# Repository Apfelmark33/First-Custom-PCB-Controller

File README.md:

# Pathfinder 

A custom, password-protected PCB controller board that acts as a digital combination lock system. It's essentially a safe but without anything in it (yet). 

I used KICad to make the pbc and the arduino IDE for the code.

---

##  Project Overview

How it Works
Pathfinder is a simple electronic lock system that uses 3 buttons to enter a password. As you press the buttons, LEDs light up to show your progress, and a small speaker (piezo buzzer) plays different sounds to let you know if your password was right or wrong.

Key Features
Smart Code Checking: Instead of just adding numbers together (where the order doesn't matter), the board remembers the exact sequence of your button presses. If your password is "abc", typing "cba" won't open it!

Every time you press a button, an LED turns on. By the third press, all three LEDs light up so you know you've entered the full 3-character code (a 3 character code is necessary but it can always be changed in the firmware)

Sound Alerts: The system talks to you through sound (so you know it works). It plays a happy, double-beep if you get the password right, and a low, buzzing tone if you get it wrong (room for improvement).

## Schematic

## PCB Layout

## 3D Model

## Bill of Materials (BOM)

| Name | Purpose | Quantity | Total Cost (USD) | Link | Distributor |
| :--- | :--- | :---: | :---: | :--- | :--- |
| **Custom PCB** | PCB | 1 | 1.75 | [Link](https://cart.jlcpcb.com/quote?stencilLayer=1&stencilWidth=100&stencilLength=100&stencilCounts=5&plateType=1&spm=Jlcpcb.Homepage.1010) | JLCPCB |
| **Buzzer** | Sound | 5 | 1.15 | [Link](https://de.aliexpress.com/item/1005006260328559.html) | Aliexpress |
| **Resistor** | Resistor | 100 | 0.56 | [Link](https://de.aliexpress.com/item/1005006040209297.html) | Aliexpress |
| **LED** | Light (Output) | 100 | 0.74 | [Link](https://de.aliexpress.com/item/4000857337669.html) | Aliexpress |
| **Keyboard switch** | Input | 20 | 1.29 | [Link](https://de.aliexpress.com/item/1005011838889689.html) | Aliexpress |
| **XIAO RP2040** | PCB | 1 | 4.52 | [Link](https://de.aliexpress.com/item/1005006987582110.html) | Aliexpress |

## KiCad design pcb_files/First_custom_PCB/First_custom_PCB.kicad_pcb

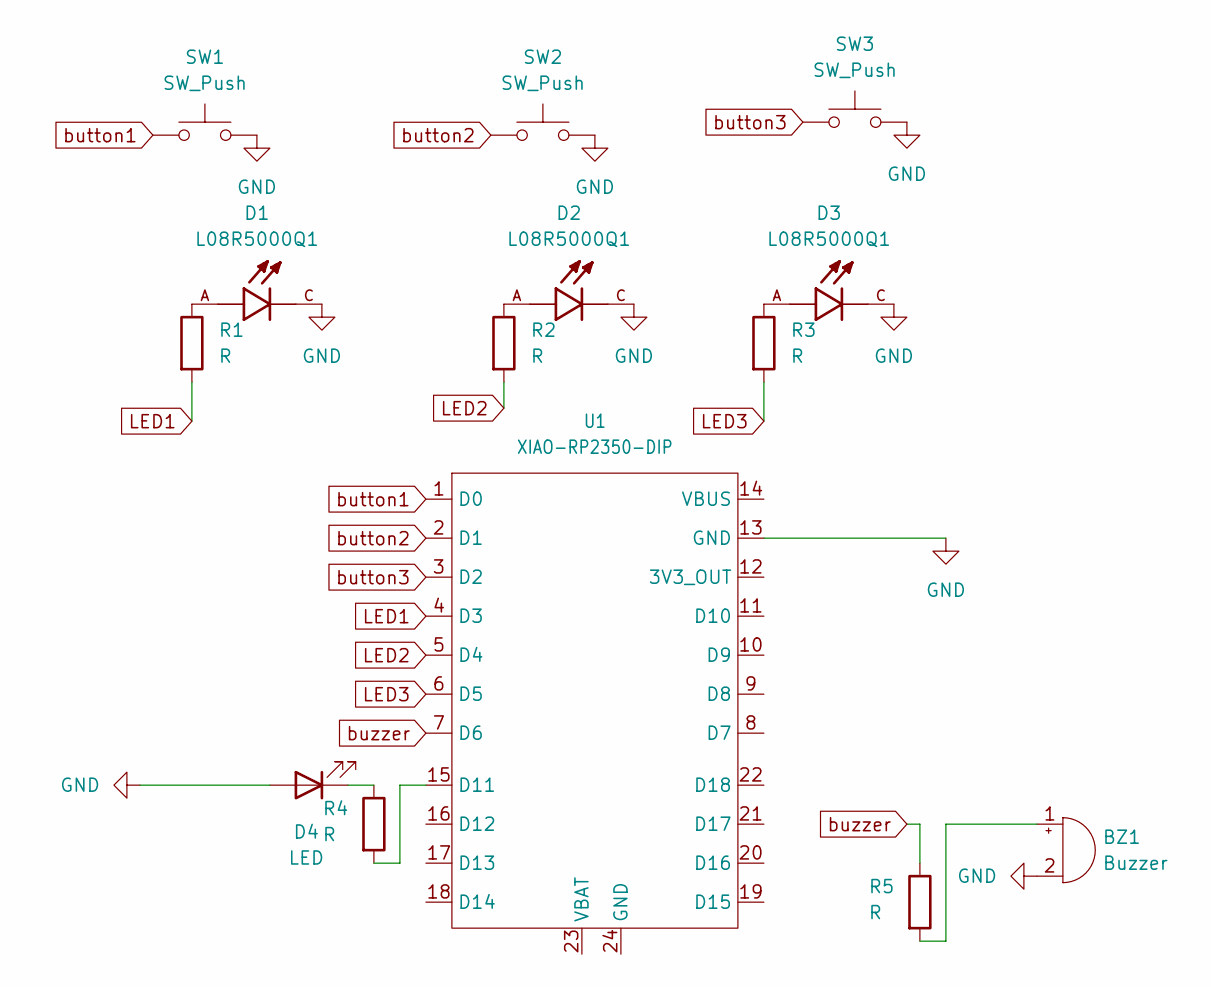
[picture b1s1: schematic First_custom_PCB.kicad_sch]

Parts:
BZ1: Buzzer; Buzzer_12x9.5RM7.6
D1, D2, D3: L08R5000Q1; LEDRD254W57D500H1070; PARTREV NA
D4: LED; LED_D5.0mm
R1, R2, R3, R4, R5: R; R_Axial_DIN0204_L3.6mm_D1.6mm_P5.08mm_Horizontal
SW1, SW2, SW3: SW_Push; SW_Cherry_MX_1.00u_PCB
U1: XIAO-RP2350-DIP

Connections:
GND: BZ1.2 (-), D1.C, D2.C, D3.C, D4.2 (A), SW1.2, SW2.2, SW3.2, U1.13 (GND)
LED1: R1.2, U1.4 (D3)
LED2: R2.2, U1.5 (D4)
LED3: R3.2, U1.6 (D5)
unnamed: BZ1.1 (+), R5.2
unnamed: D1.A, R1.1
unnamed: D2.A, R2.1
unnamed: D3.A, R3.1
unnamed: D4.1 (K), R4.1
unnamed: R4.2, U1.15 (D11)
button1: SW1.1, U1.1 (D0)
button2: SW2.1, U1.2 (D1)
button3: SW3.1, U1.3 (D2)
buzzer: R5.1, U1.7 (D6)

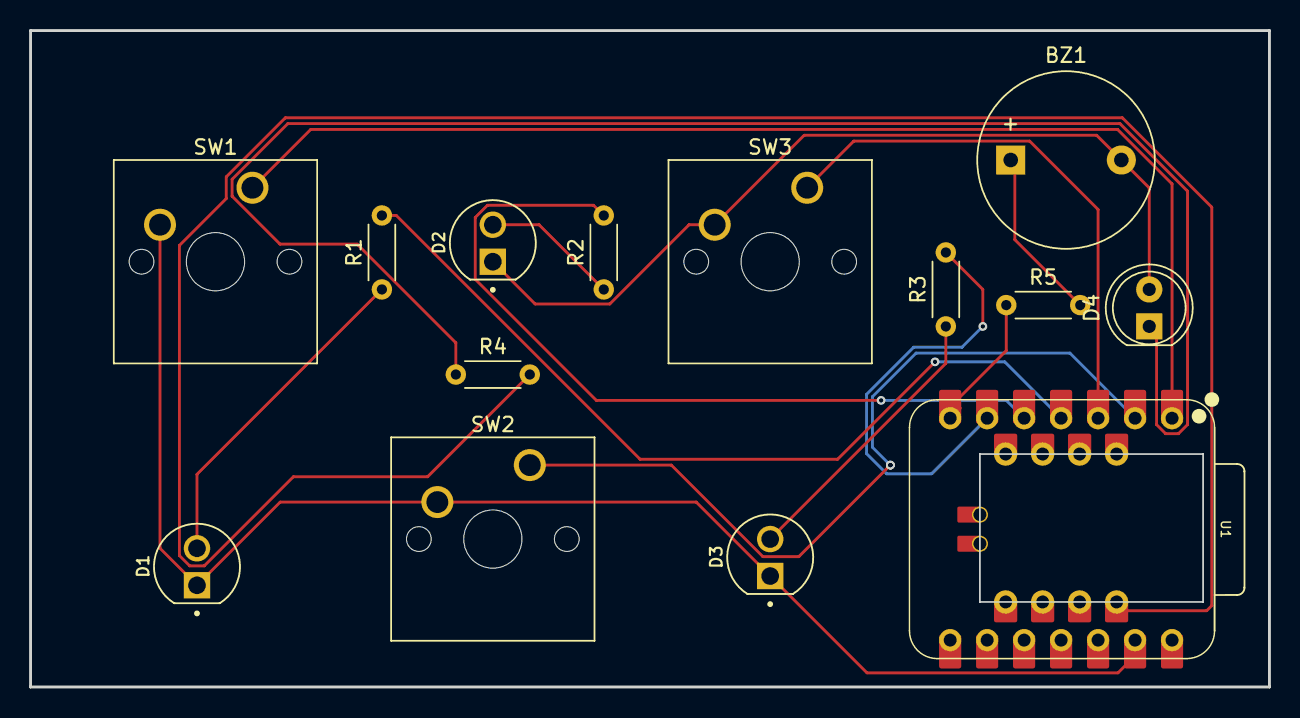
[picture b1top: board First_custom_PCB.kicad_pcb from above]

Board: 2 copper layers, 85.1 x 45.1 mm, 14 parts (0 on the bottom side), 14 nets.

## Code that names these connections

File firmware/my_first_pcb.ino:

int BUT1 = D0;
int BUT2 = D1;
int BUT3 = D2;

int LED1 = D3;
int LED2 = D4;
int LED3 = D5;

int SPEAKER = D6;
int light = D11; 


void setup() {
  // put your setup code here, to run once:

    
    pinMode(BUT1, INPUT_PULLUP);
    pinMode(BUT2, INPUT_PULLUP);
    pinMode(BUT3, INPUT_PULLUP);

    pinMode(LED1, OUTPUT);
     pinMode(LED2, OUTPUT);
    pinMode(LED3, OUTPUT);

 pinMode(SPEAKER, OUTPUT);

  pinMode(light, OUTPUT);
  digitalWrite(light, HIGH); //Standart light but customizable if necessary
}

void loop() {
  // put your main code here, to run repeatedly:

String input = "";
const String password = "abc";
boolean status = false;
for(int i= 0; i<3; i++){
while (status == false){


if(digitalRead(BUT1) == LOW){

tone(SPEAKER, 1000);
input = input +"a";
status = true;
delay(100);
}
else if(digitalRead(BUT2) == LOW){
  
tone(SPEAKER, 1000);
input = input +"b";
status = true;
delay(100);
}


else if(digitalRead(BUT3) == LOW){

tone(SPEAKER, 1000);
input = input +"c";
status = true;
delay(100);

}
}
noTone(SPEAKER);
status = false;

if(i == 0){
   digitalWrite(LED1, HIGH); 
}
else if(i == 1){
   digitalWrite(LED2, HIGH); 
}
else if(i == 2){
   digitalWrite(LED3, HIGH); 
}

}

//password
if(input == password){
tone(speakerPin, 600, 100); 
  delay(120);                 
  tone(SPEAKER, 900, 250);  
  delay(250);
}else{
tone(speakerPin, 180, 400);  
  delay(400);
    digitalWrite(LED1, LOW); 
      digitalWrite(LED2, LOW); 
        digitalWrite(LED3, LOW); 
}

}

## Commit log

2026-06-24 Added the pcb files
2026-06-24 added the firmware
2026-06-24 Create README.md with project details and images
    Added project overview, features, and images for schematic, PCB, and 3D model.
2026-06-25 Enhance README with PCB Layout and BOM section
    Added Bill of Materials (BOM) section with details on components used, including links and costs.
2026-06-25 Fix typo in Custom PBC to Custom PCB
